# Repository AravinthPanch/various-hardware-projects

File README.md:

# various-hardware-projects
Collection of various PCB designs and Firmware for prototyping projects

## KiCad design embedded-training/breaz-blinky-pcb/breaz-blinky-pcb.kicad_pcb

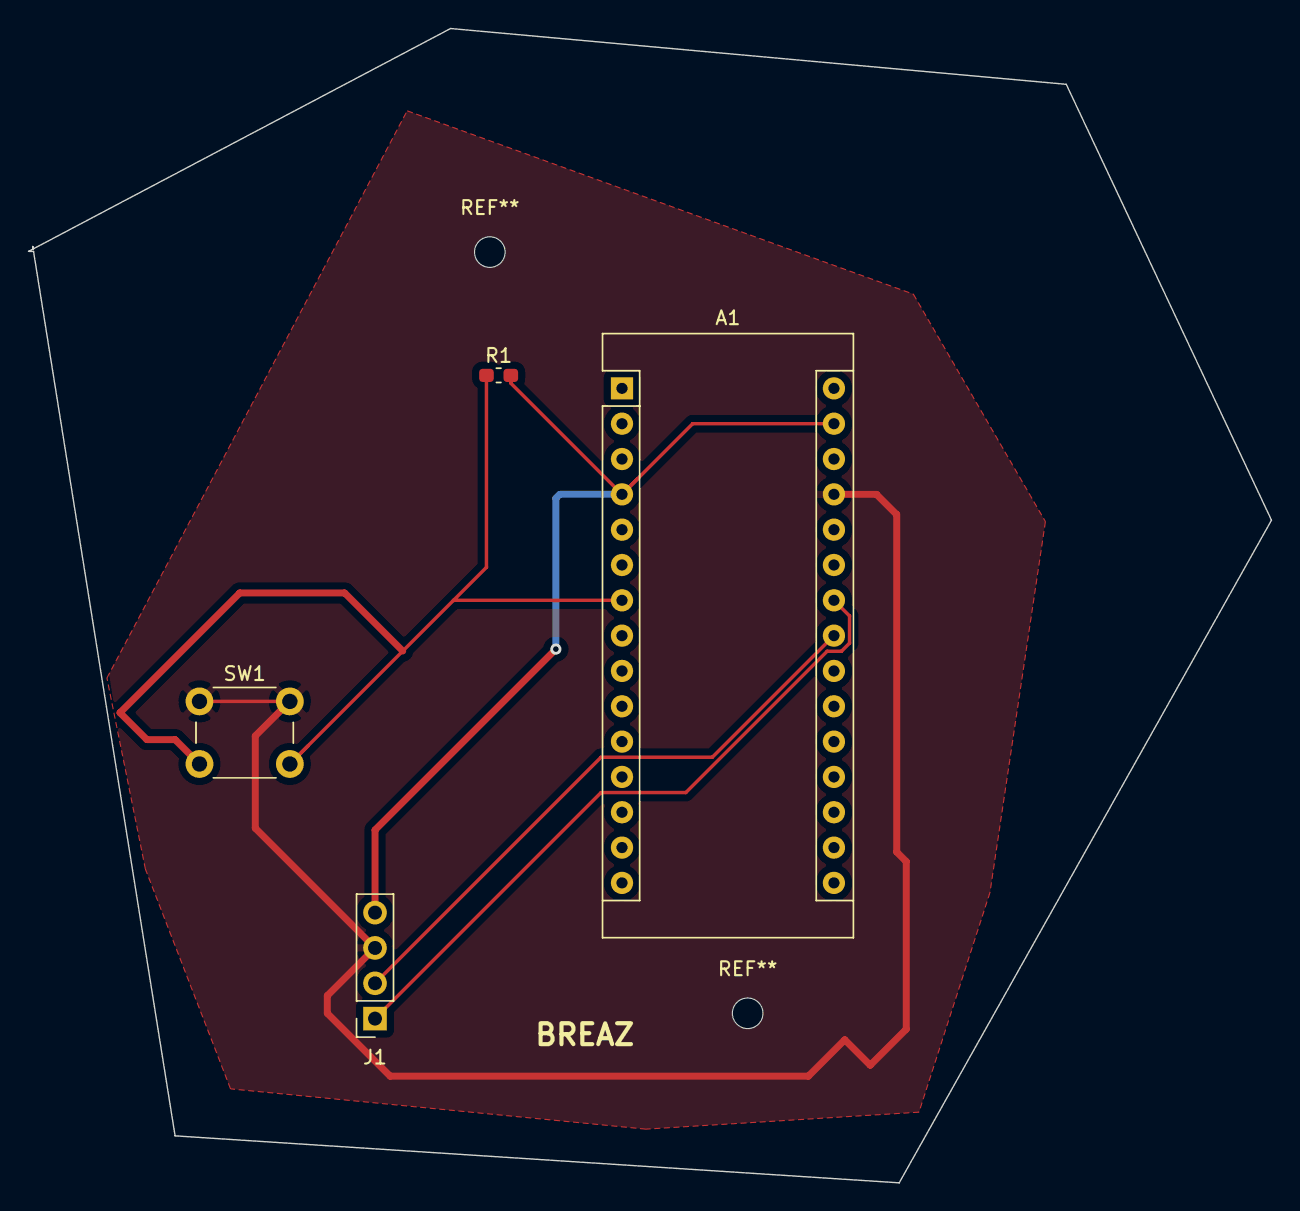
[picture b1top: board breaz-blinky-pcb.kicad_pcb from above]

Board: 2 copper layers, 89.4 x 83.0 mm, 4 parts (0 on the bottom side), 5 nets.

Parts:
A1: Arduino_Nano_v3.x; Arduino_Nano
J1: ssd1306-oled; PinSocket_1x04_P2.54mm_Vertical
R1: 10K; R_0603_1608Metric_Pad1.05x0.95mm_HandSolder
SW1: button; SW_PUSH_6mm

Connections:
+5V: A1.27, J1.3, SW1.1
unnamed: A1.7, R1.1, SW1.2
unnamed: A1.23, J1.2
unnamed: A1.24, J1.1
unnamed: A1.4, A1.29, J1.4, R1.2

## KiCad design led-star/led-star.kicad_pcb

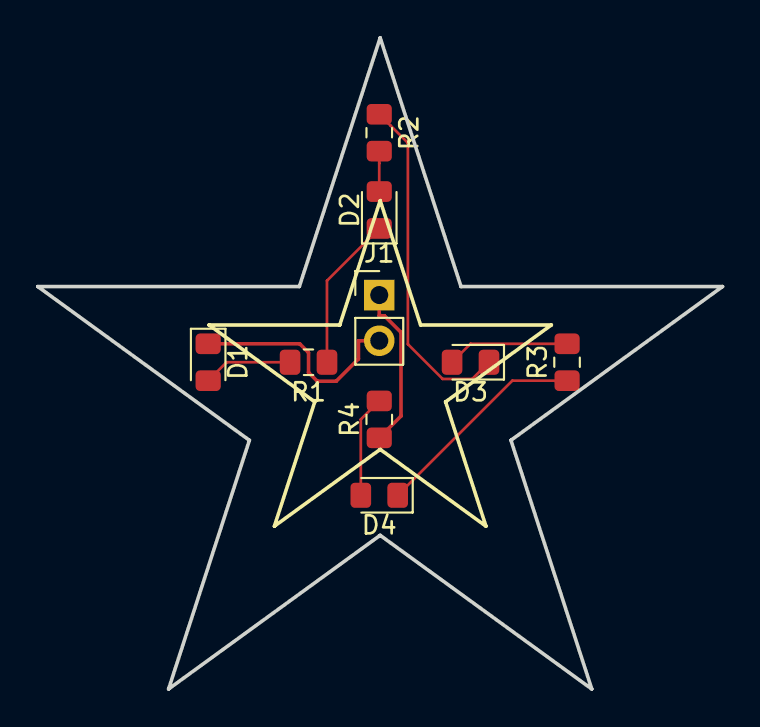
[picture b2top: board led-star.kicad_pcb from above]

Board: 2 copper layers, 38.0 x 36.2 mm, 9 parts (0 on the bottom side), 9 nets.

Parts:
D1, D2, D3, D4: RED; LED_0805_2012Metric_Pad1.15x1.40mm_HandSolder
J1: VIN; PinHeader_1x02_P2.54mm_Vertical
R1, R2, R3, R4: 1K; R_0805_2012Metric_Pad1.15x1.40mm_HandSolder

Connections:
/GND: D1.1, J1.2
/VCC: J1.1, R4.1
unnamed: D1.2, R1.2
unnamed: D2.1, R1.1
unnamed: D2.2, R2.2
unnamed: D3.1, R2.1
unnamed: D3.2, R3.2
unnamed: D4.1, R3.1
unnamed: D4.2, R4.2

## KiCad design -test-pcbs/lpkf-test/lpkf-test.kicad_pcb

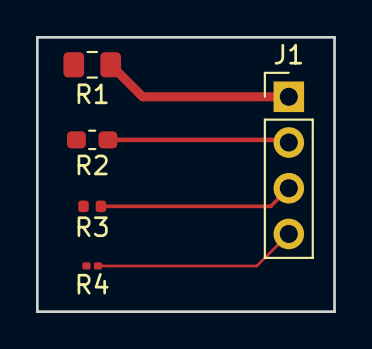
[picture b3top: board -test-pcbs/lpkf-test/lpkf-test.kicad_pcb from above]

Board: 2 copper layers, 16.5 x 15.2 mm, 5 parts (0 on the bottom side), 4 nets.

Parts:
J1: Conn_01x04; PinHeader_1x04_P2.54mm_Vertical
R1: R_Small; R_0805_2012Metric_Pad1.15x1.40mm_HandSolder
R2: R_Small; R_0603_1608Metric_Pad1.05x0.95mm_HandSolder
R3: R_Small; R_0402_1005Metric
R4: R_Small; R_0201_0603Metric

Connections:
unnamed: J1.1, R1.1
unnamed: J1.2, R2.1
unnamed: J1.3, R3.1
unnamed: J1.4, R4.1

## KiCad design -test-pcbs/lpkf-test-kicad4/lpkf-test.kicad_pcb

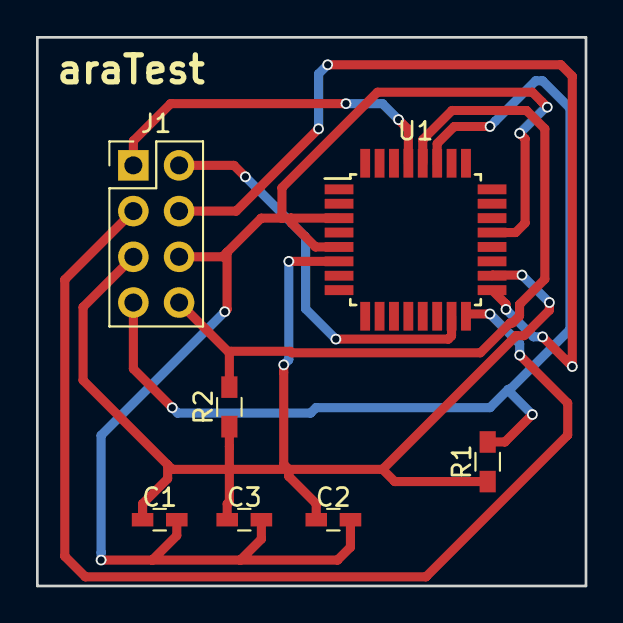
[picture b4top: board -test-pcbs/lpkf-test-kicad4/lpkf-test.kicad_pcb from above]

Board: 2 copper layers, 30.5 x 30.5 mm, 7 parts (0 on the bottom side), 8 nets.

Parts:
C1, C2, C3: 0.1uF; C_0603_HandSoldering
J1: 02x04; Pin_Header_Straight_2x04_Pitch2.54mm
R1, R2: 10K; R_0603_HandSoldering
U1: ATMEGA168PA-AU; TQFP-32_7x7mm_Pitch0.8mm

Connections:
+5V: C1.1, C2.1, C3.1, J1.5, R1.1, R2.1, U1.4, U1.6, U1.18
/SCL: J1.8, R2.2, U1.28
/SDA: J1.7, R1.2, U1.27
GND: C1.2, C2.2, C3.2, J1.6, U1.3, U1.5, U1.21
unnamed: J1.1, U1.29
unnamed: J1.2, U1.15
unnamed: J1.3, U1.16
unnamed: J1.4, U1.17

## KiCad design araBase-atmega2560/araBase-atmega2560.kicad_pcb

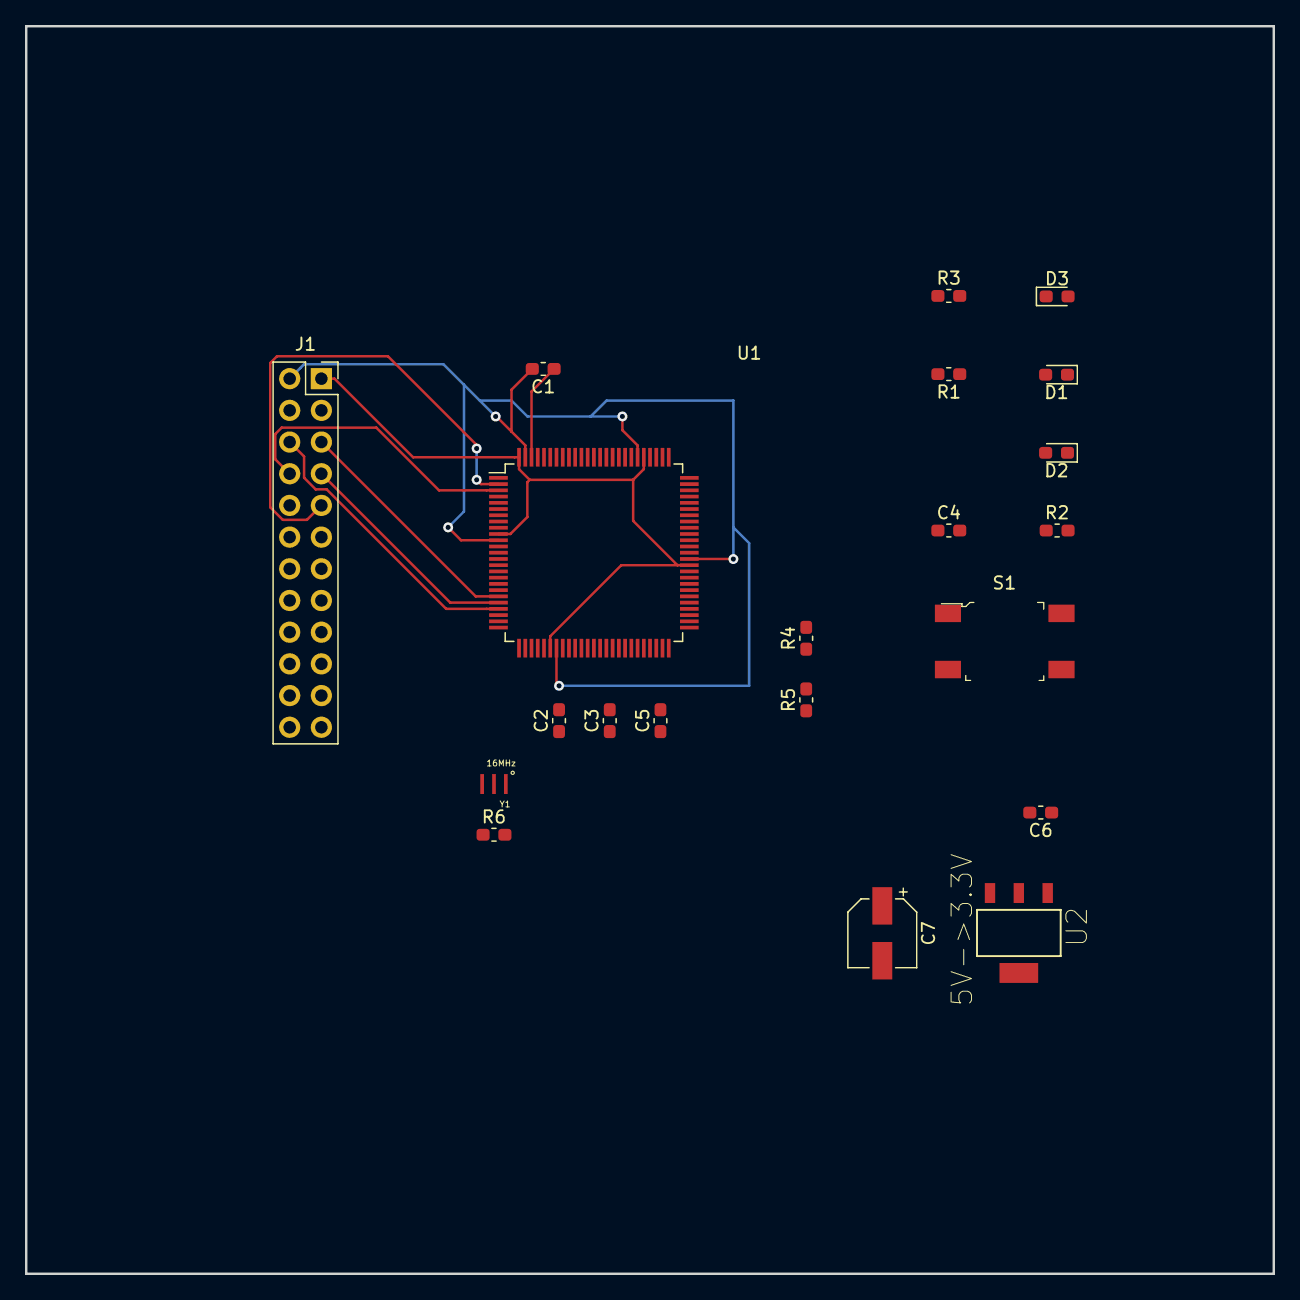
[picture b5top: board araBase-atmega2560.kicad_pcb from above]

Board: 2 copper layers, 100.0 x 100.0 mm, 21 parts (0 on the bottom side), 30 nets.

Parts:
C1, C2, C3, C5: 0.1uF; C_0603_1608Metric_Pad1.05x0.95mm_HandSolder
C4: 22pF; C_0603_1608Metric_Pad1.05x0.95mm_HandSolder
C6: 100nF; C_0603_1608Metric_Pad1.05x0.95mm_HandSolder
C7: 33uF; CP_Elec_5x5.8
D1: LED-Y; LED_0603_1608Metric_Pad1.05x0.95mm_HandSolder
D2: 100V; D_0603_1608Metric_Pad1.05x0.95mm_HandSolder
D3: LED-G; LED_0603_1608Metric_Pad1.05x0.95mm_HandSolder
J1: UI; PinSocket_2x12_P2.54mm_Vertical
R1, R2, R3, R4, R5: 10K; R_0603_1608Metric_Pad1.05x0.95mm_HandSolder
R6: 1M; R_0603_1608Metric_Pad1.05x0.95mm_HandSolder
S1: RESET-SW; Switch_Tactile_SMD_6x6mm
U1: ATmega2560-16AU; TQFP-100_14x14mm_P0.5mm
U2: 5V->3.3V; SOT230P696X180-4N
Y1: 16MHz; OSC_CSTCE16M0V53-R0

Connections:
+5V: C2.1, C3.1, C5.1, C6.1, D2.1, J1.1, R2.2, R3.1, R4.2, R5.2, U1.10, U1.31, U1.61, U1.80, U1.100, U2.1
/3.3V: C7.1, J1.3, U2.3
/A0: J1.13, U1.97
/A1: J1.14, U1.96
/A2: J1.15, U1.95
/A3: J1.16, U1.94
/A4: J1.17, U1.93
/A5: J1.18, U1.92
/AREF: C1.1, J1.12, U1.98
/D2: J1.19, U1.6
/D3: J1.20, U1.7
/D4: J1.21, U1.1
/D5: J1.22, U1.5
/D6: J1.23, U1.15
/D7: J1.24, U1.16
/MISO: J1.6, U1.22
/MOSI: J1.7, U1.21
/RESET: C4.1, D2.2, J1.4, R2.1
/RX0: J1.9, U1.2
/SCK: J1.5, U1.20
/SCL: J1.11, R4.1, U1.43
/SDA: J1.10, R5.1, U1.44
/TX0: J1.8, U1.3
GND: C1.2, C2.2, C3.2, C4.2, C5.2, C6.2, C7.2, D1.1, D3.1, J1.2, S1.1, S1.2, U1.11, U1.32, U1.62, U1.81, U1.99, U2.2, U2.4, Y1.2
unnamed: D1.2, R1.2
unnamed: D3.2, R3.2
unnamed: R1.1, U1.13
unnamed: R6.1, U1.33, Y1.3
unnamed: R6.2, U1.34, Y1.1
unnamed: S1.3, S1.4, U1.30

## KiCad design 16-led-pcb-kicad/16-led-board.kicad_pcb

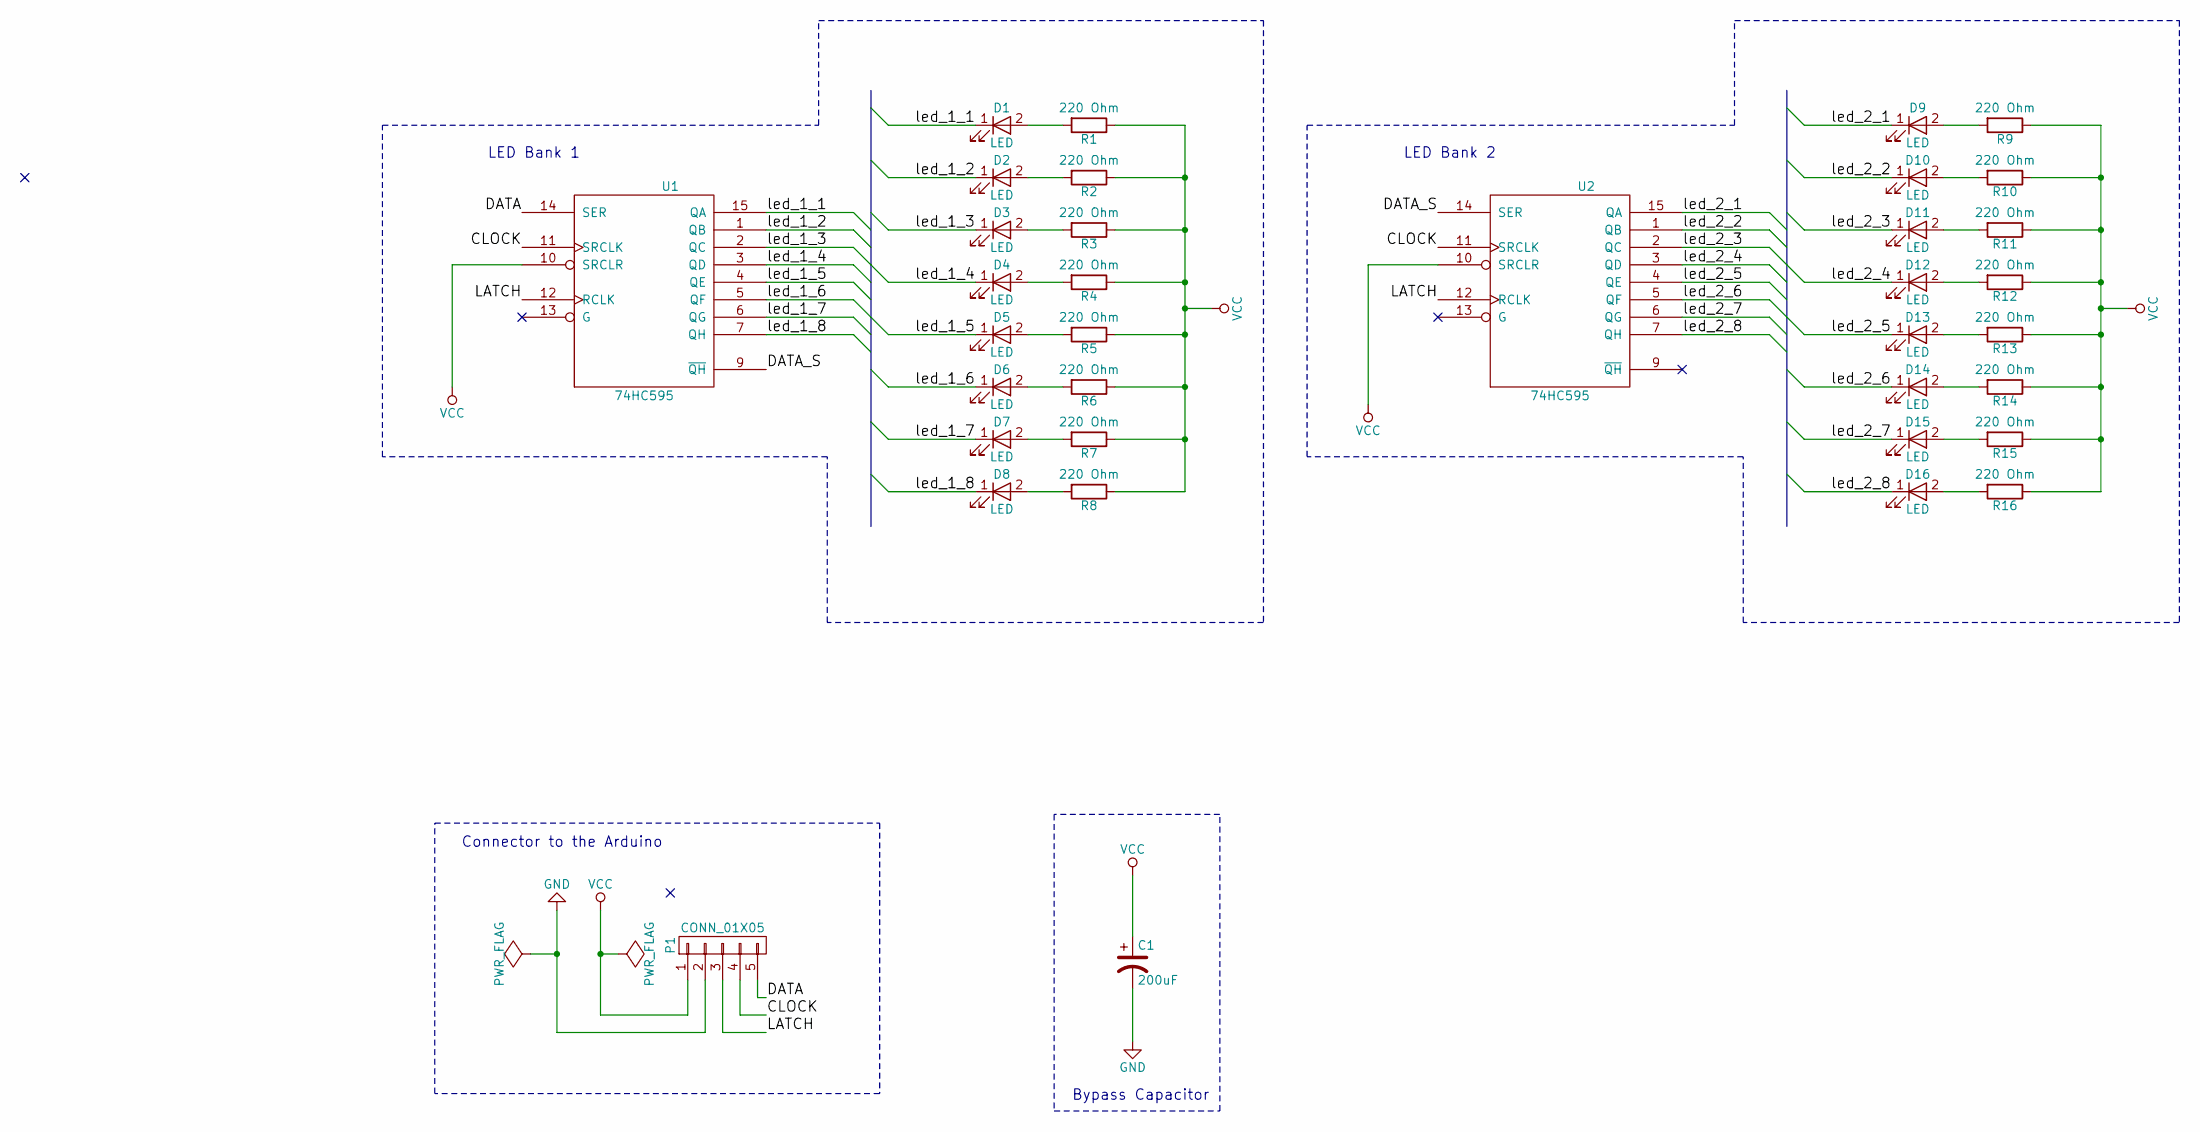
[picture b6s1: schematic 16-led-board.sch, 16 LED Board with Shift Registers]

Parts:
C1: 200uF; CP_Elec_6.3x5.3
D1, D2, D3, D4, D5, D6, D7, D8, D9, D10, D11, D12, D13, D14, D15, D16: LED; LED_0805
P1: CONN_01X05; Pin_Header_Straight_1x05_Pitch2.54mm
R1, R2, R3, R4, R5, R6, R7, R8, R9, R10, R11, R12, R13, R14, R15, R16: 220 Ohm; R_0805_HandSoldering
U1, U2: 74HC595; SO-16-N

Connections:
/CLOCK: P1.4, U1.11 (SRCLK), U2.11 (SRCLK)
/DATA: P1.5, U1.14 (SER)
/DATA_S: U1.9 (~QH), U2.14 (SER)
/LATCH: P1.3, U1.12 (RCLK), U2.12 (RCLK)
/led_1_1: D1.1 (K), U1.15 (QA)
/led_1_2: D2.1 (K), U1.1 (QB)
/led_1_3: D3.1 (K), U1.2 (QC)
/led_1_4: D4.1 (K), U1.3 (QD)
/led_1_5: D5.1 (K), U1.4 (QE)
/led_1_6: D6.1 (K), U1.5 (QF)
/led_1_7: D7.1 (K), U1.6 (QG)
/led_1_8: D8.1 (K), U1.7 (QH)
/led_2_1: D9.1 (K), U2.15 (QA)
/led_2_2: D10.1 (K), U2.1 (QB)
/led_2_3: D11.1 (K), U2.2 (QC)
/led_2_4: D12.1 (K), U2.3 (QD)
/led_2_5: D13.1 (K), U2.4 (QE)
/led_2_6: D14.1 (K), U2.5 (QF)
/led_2_7: D15.1 (K), U2.6 (QG)
/led_2_8: D16.1 (K), U2.7 (QH)
GND: C1.2, P1.2, U1.8 (GND), U2.8 (GND)
unnamed: D1.2 (A), R1.2
unnamed: D2.2 (A), R2.2
unnamed: D3.2 (A), R3.2
unnamed: D4.2 (A), R4.2
unnamed: D5.2 (A), R5.2
unnamed: D6.2 (A), R6.2
unnamed: D7.2 (A), R7.2
unnamed: D8.2 (A), R8.2
unnamed: D9.2 (A), R9.2
unnamed: D10.2 (A), R10.2
unnamed: D11.2 (A), R11.2
unnamed: D12.2 (A), R12.2
unnamed: D13.2 (A), R13.2
unnamed: D14.2 (A), R14.2
unnamed: D15.2 (A), R15.2
unnamed: D16.2 (A), R16.2
VCC: C1.1, P1.1, R1.1, R2.1, R3.1, R4.1, R5.1, R6.1, R7.1, R8.1, R9.1, R10.1, R11.1, R12.1, R13.1, R14.1, R15.1, R16.1, U1.10 (SRCLR), U1.16 (VCC), U2.10 (SRCLR), U2.16 (VCC)

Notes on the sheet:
Connector to the Arduino
Bypass Capacitor
LED Bank 2
LED Bank 1

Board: 2 copper layers, 36 parts (0 on the bottom side), 38 nets, no tracks yet.

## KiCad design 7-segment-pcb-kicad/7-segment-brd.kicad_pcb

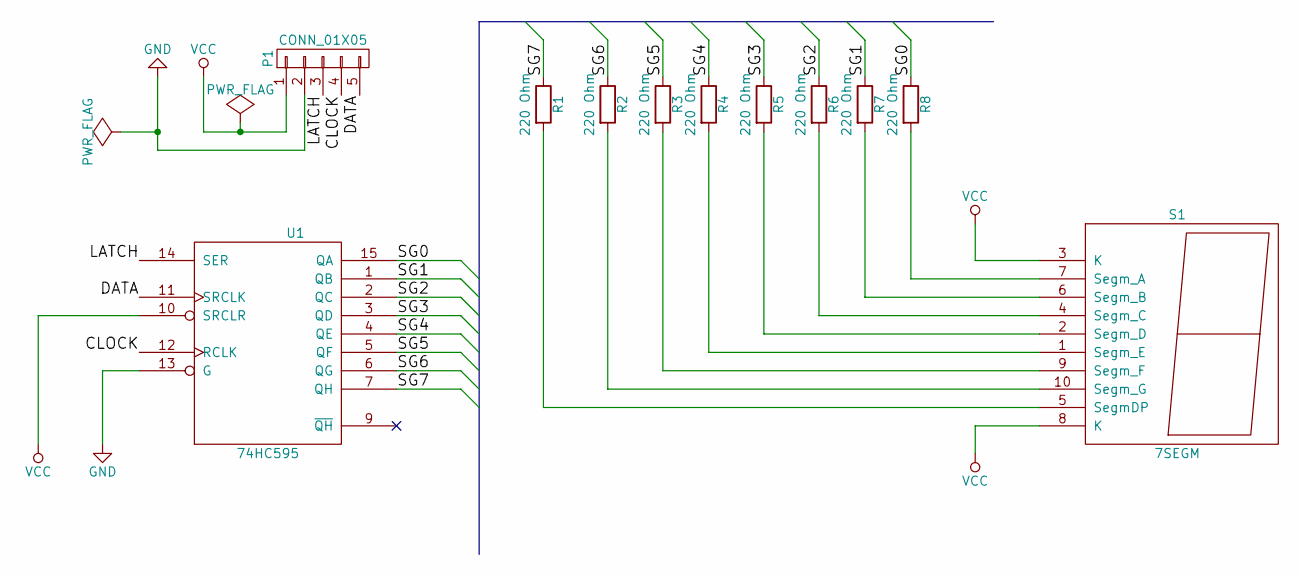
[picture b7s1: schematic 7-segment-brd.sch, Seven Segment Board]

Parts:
P1: CONN_01X05; Pin_Header_Straight_1x05_Pitch2.54mm
R1, R2, R3, R4, R5, R6, R7, R8: 220 Ohm; R_Axial_DIN0207_L6.3mm_D2.5mm_P10.16mm_Horizontal
S1: 7SEGM; 7SegmentLED_LTS6760_LTS6780
U1: 74HC595; DIP-16_W7.62mm

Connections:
/CLOCK: P1.4, U1.12 (RCLK)
/DATA: P1.5, U1.11 (SRCLK)
/LATCH: P1.3, U1.14 (SER)
/SG0: R8.1, U1.15 (QA)
/SG1: R7.1, U1.1 (QB)
/SG2: R6.1, U1.2 (QC)
/SG3: R5.1, U1.3 (QD)
/SG4: R4.1, U1.4 (QE)
/SG5: R3.1, U1.5 (QF)
/SG6: R2.1, U1.6 (QG)
/SG7: R1.1, U1.7 (QH)
GND: P1.2, U1.8 (GND), U1.13 (G)
unnamed: R1.2, S1.5 (SegmDP)
unnamed: R2.2, S1.10 (Segm_G)
unnamed: R3.2, S1.9 (Segm_F)
unnamed: R4.2, S1.1 (Segm_E)
unnamed: R5.2, S1.2 (Segm_D)
unnamed: R6.2, S1.4 (Segm_C)
unnamed: R7.2, S1.6 (Segm_B)
unnamed: R8.2, S1.7 (Segm_A)
VCC: P1.1, S1.3 (K), S1.8 (K), U1.10 (SRCLR), U1.16 (VCC)

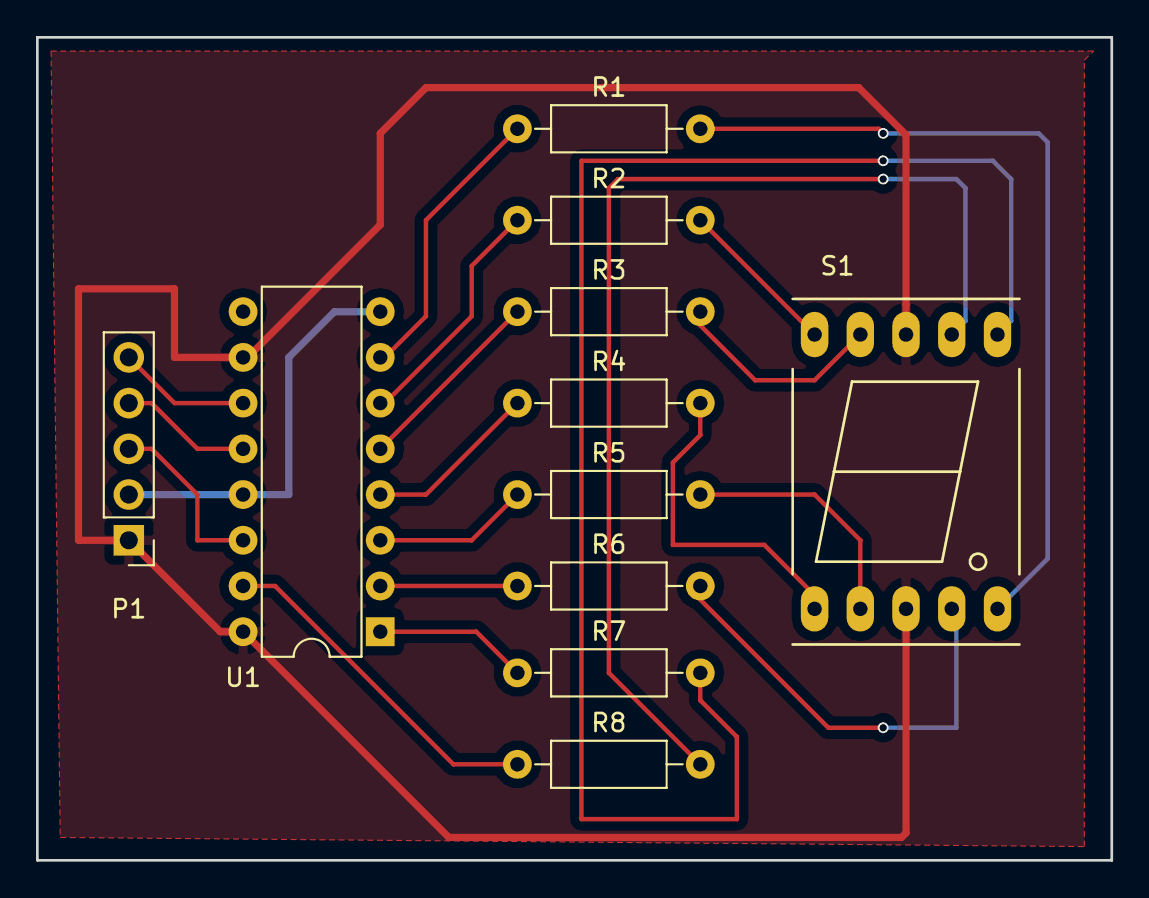
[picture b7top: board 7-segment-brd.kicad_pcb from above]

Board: 2 copper layers, 59.7 x 45.7 mm, 11 parts (0 on the bottom side), 21 nets.

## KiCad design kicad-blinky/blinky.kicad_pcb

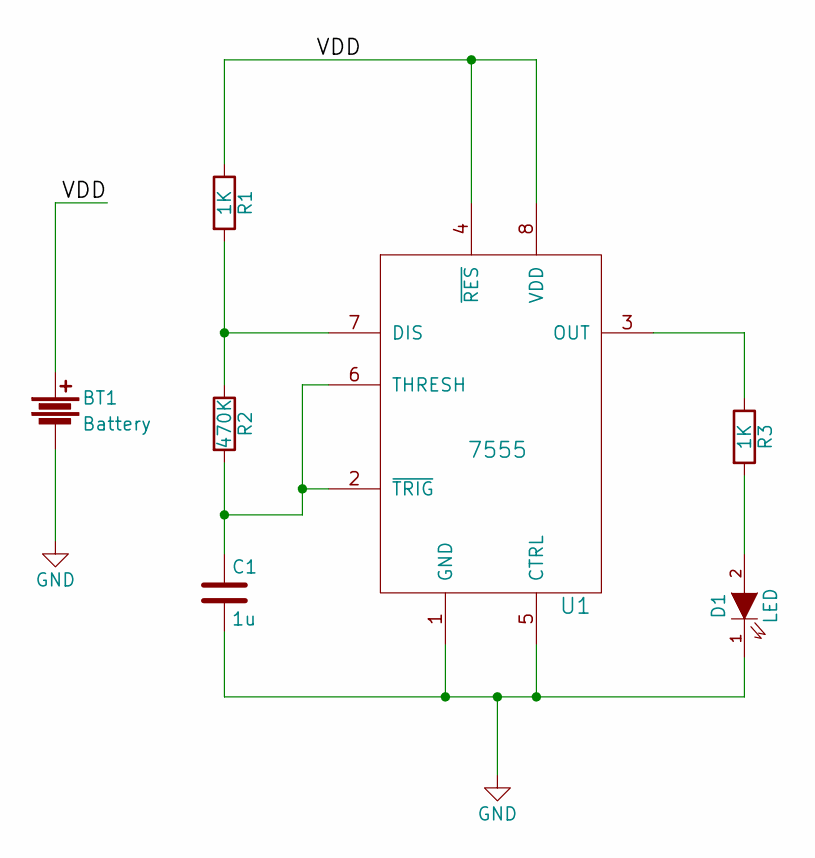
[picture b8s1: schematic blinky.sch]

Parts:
BT1: Battery; S8221
C1: 1u; C_1206_HandSoldering
D1: LED; LED_0805
R1, R3: 1K; R_0805_HandSoldering
R2: 470K; R_0805_HandSoldering
U1: 7555; SOIC-8_3.9x4.9mm_Pitch1.27mm

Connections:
/VDD: BT1.1, R1.1, U1.4 (~RES), U1.8 (VDD)
GND: BT1.2, C1.2, D1.1 (K), U1.1 (GND), U1.5 (CTRL)
unnamed: C1.1, R2.2, U1.2 (~TRIG), U1.6 (THRESH)
unnamed: D1.2 (A), R3.2
unnamed: R1.2, R2.1, U1.7 (DIS)
unnamed: R3.1, U1.3 (OUT)

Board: 2 copper layers, 7 parts (1 on the bottom side), 6 nets, no tracks yet.

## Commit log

2017-08-27 Add LED PWM Lamp prototypes and Electron App
2018-10-29 Add arabeat atmega2560 project
2018-10-29 Add atmega baseboard
2018-10-29 Add test board for IPKF machine
2018-10-29 Add nano led matrix
2019-01-04 Add LPKF test PCB, clean files
2019-01-12 Add SMD test pcb for LPKF
2019-07-09 Add led star project
2019-10-12 Add apache 2.0 opensource licence
2020-07-07 Bump electron in /led-lamp-proto/proto-2/lamp_tx_electron_app
    Bumps [electron](https://github.com/electron/electron) from 1.8.8 to 9.1.0.
    - [Release notes](https://github.com/electron/electron/releases)
    - [Changelog](https://github.com/electron/electron/blob/master/docs/breaking-changes.md)
    - [Commits](https://github.com/electron/electron/compare/v1.8.8...v9.1.0)
2021-03-29 Add Ad5933 prototype
2022-05-02 Add qm qpc blinky
2022-05-04 Add STM32 L152RE Nuclueo
2022-05-05 Add startup training project
2022-05-05 Update qm blinky
2022-05-05 Add dpp example for nucleo-l152re
2022-05-05 Clean up dpp example
2022-05-05 Update gitignore
